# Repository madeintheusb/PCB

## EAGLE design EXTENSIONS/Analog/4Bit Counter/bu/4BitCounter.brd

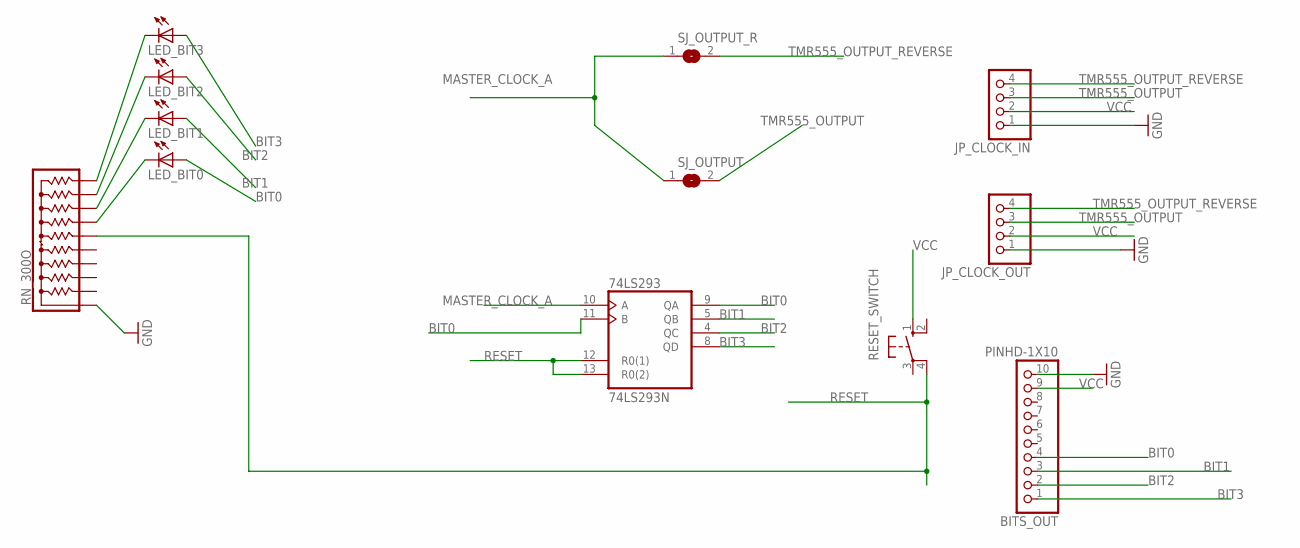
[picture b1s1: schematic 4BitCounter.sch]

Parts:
74LS293: 74LS293N; DIL14
BITS_OUT: PINHD-1X10; 1X10-BIG
JP_CLOCK_IN: PINHD-1X4; 1X04
JP_CLOCK_OUT: PINHD-1X4; 1X04
LED_BIT0, LED_BIT1, LED_BIT2, LED_BIT3: LEDSMT1206; 1206
RESET_SWITCH: 10-XX; B3F-10XX
RN_300O: 4610X; SIP10
SJ_OUTPUT: SOLDERJUMPERREFLOW; SOLDERJUMPER_REFLOW
SJ_OUTPUT_R: SOLDERJUMPERREFLOW; SOLDERJUMPER_REFLOW

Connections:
BIT0: 74LS293.9 (QA), 74LS293.11 (B), BITS_OUT.4, LED_BIT0.A
BIT1: 74LS293.5 (QB), BITS_OUT.3, LED_BIT1.A
BIT2: 74LS293.4 (QC), BITS_OUT.2, LED_BIT2.A
BIT3: 74LS293.8 (QD), BITS_OUT.1, LED_BIT3.A
GND: 74LS293.7 (GND), BITS_OUT.10, JP_CLOCK_IN.1, JP_CLOCK_OUT.1, RN_300O.1
MASTER_CLOCK_A: 74LS293.10 (A), SJ_OUTPUT.1, SJ_OUTPUT_R.1
unnamed: LED_BIT1.C, RN_300O.8
unnamed: LED_BIT0.C, RN_300O.7
unnamed: LED_BIT2.C, RN_300O.9
unnamed: LED_BIT3.C, RN_300O.10
RESET: 74LS293.12 (R0(1)), 74LS293.13 (R0(2)), RESET_SWITCH.4 (P1), RN_300O.6
TMR555_OUTPUT: JP_CLOCK_IN.3, JP_CLOCK_OUT.3, SJ_OUTPUT.2
TMR555_OUTPUT_REVERSE: JP_CLOCK_IN.4, JP_CLOCK_OUT.4, SJ_OUTPUT_R.2
VCC: 74LS293.14 (VCC), BITS_OUT.9, JP_CLOCK_IN.2, JP_CLOCK_OUT.2, RESET_SWITCH.1 (S)

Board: 2 copper layers, 12 parts (0 on the bottom side), 14 nets, no tracks yet.

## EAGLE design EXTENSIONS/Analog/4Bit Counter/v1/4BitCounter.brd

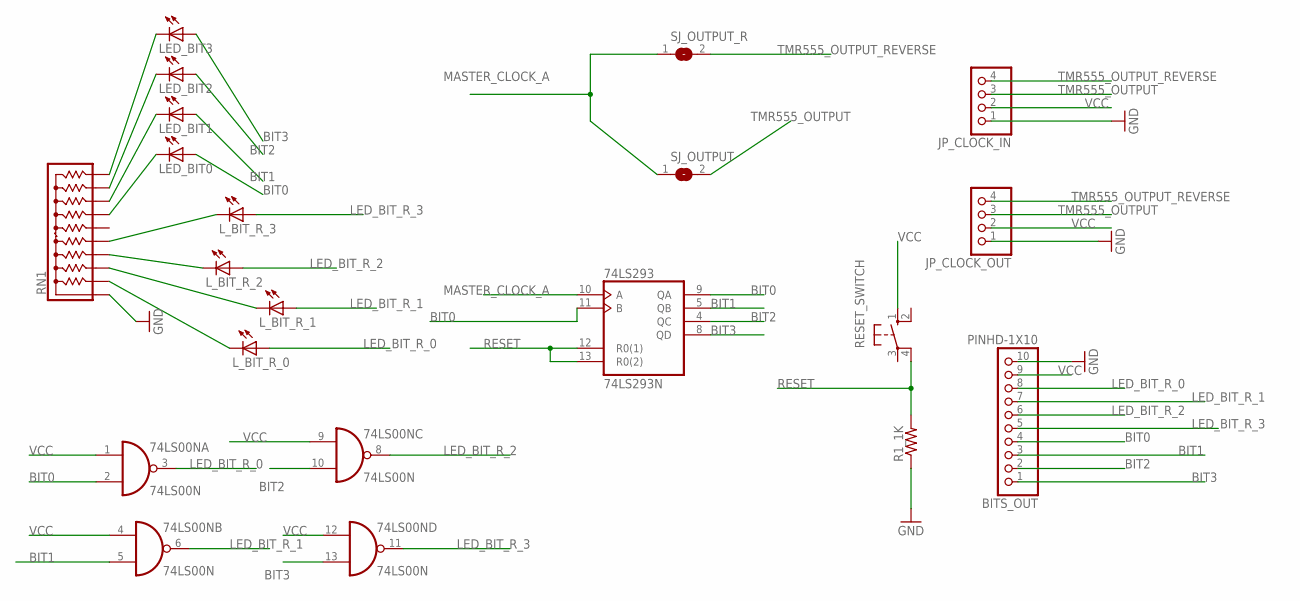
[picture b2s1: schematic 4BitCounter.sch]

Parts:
74LS00N: 74LS00N; DIL14
74LS293: 74LS293N; DIL14
BITS_OUT: PINHD-1X10; 1X10-BIG
JP_CLOCK_IN: PINHD-1X4; 1X04
JP_CLOCK_OUT: PINHD-1X4; 1X04
LED_BIT0, LED_BIT1, LED_BIT2, LED_BIT3: LEDSMT1206; 1206
L_BIT_R_0, L_BIT_R_1, L_BIT_R_2, L_BIT_R_3: LEDSMT1206; 1206
R1_1K: R-US_R1206; R1206
RESET_SWITCH: 10-XX; B3F-10XX
RN1: 4610X; SIP10
SJ_OUTPUT: SOLDERJUMPERREFLOW; SOLDERJUMPER_REFLOW
SJ_OUTPUT_R: SOLDERJUMPERREFLOW; SOLDERJUMPER_REFLOW

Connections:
BIT0: 74LS00N.2 (I1), 74LS293.9 (QA), 74LS293.11 (B), BITS_OUT.4, LED_BIT0.A
BIT1: 74LS00N.5 (I1), 74LS293.5 (QB), BITS_OUT.3, LED_BIT1.A
BIT2: 74LS00N.10 (I1), 74LS293.4 (QC), BITS_OUT.2, LED_BIT2.A
BIT3: 74LS00N.13 (I1), 74LS293.8 (QD), BITS_OUT.1, LED_BIT3.A
GND: 74LS00N.7 (GND), 74LS293.7 (GND), BITS_OUT.10, JP_CLOCK_IN.1, JP_CLOCK_OUT.1, R1_1K.1, RN1.1
LED_BIT_R_0: 74LS00N.3 (O), BITS_OUT.8, L_BIT_R_0.A
LED_BIT_R_1: 74LS00N.6 (O), BITS_OUT.7, L_BIT_R_1.A
LED_BIT_R_2: 74LS00N.8 (O), BITS_OUT.6, L_BIT_R_2.A
LED_BIT_R_3: 74LS00N.11 (O), BITS_OUT.5, L_BIT_R_3.A
MASTER_CLOCK_A: 74LS293.10 (A), SJ_OUTPUT.1, SJ_OUTPUT_R.1
unnamed: LED_BIT1.C, RN1.8
unnamed: LED_BIT0.C, RN1.7
unnamed: LED_BIT2.C, RN1.9
unnamed: LED_BIT3.C, RN1.10
unnamed: L_BIT_R_0.C, RN1.2
unnamed: L_BIT_R_1.C, RN1.3
unnamed: L_BIT_R_2.C, RN1.4
unnamed: L_BIT_R_3.C, RN1.5
RESET: 74LS293.12 (R0(1)), 74LS293.13 (R0(2)), R1_1K.2, RESET_SWITCH.4 (P1)
TMR555_OUTPUT: JP_CLOCK_IN.3, JP_CLOCK_OUT.3, SJ_OUTPUT.2
TMR555_OUTPUT_REVERSE: JP_CLOCK_IN.4, JP_CLOCK_OUT.4, SJ_OUTPUT_R.2
VCC: 74LS00N.1 (I0), 74LS00N.4 (I0), 74LS00N.9 (I0), 74LS00N.12 (I0), 74LS00N.14 (VCC), 74LS293.14 (VCC), BITS_OUT.9, JP_CLOCK_IN.2, JP_CLOCK_OUT.2, RESET_SWITCH.1 (S)

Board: 2 copper layers, 18 parts (0 on the bottom side), 22 nets, no tracks yet.

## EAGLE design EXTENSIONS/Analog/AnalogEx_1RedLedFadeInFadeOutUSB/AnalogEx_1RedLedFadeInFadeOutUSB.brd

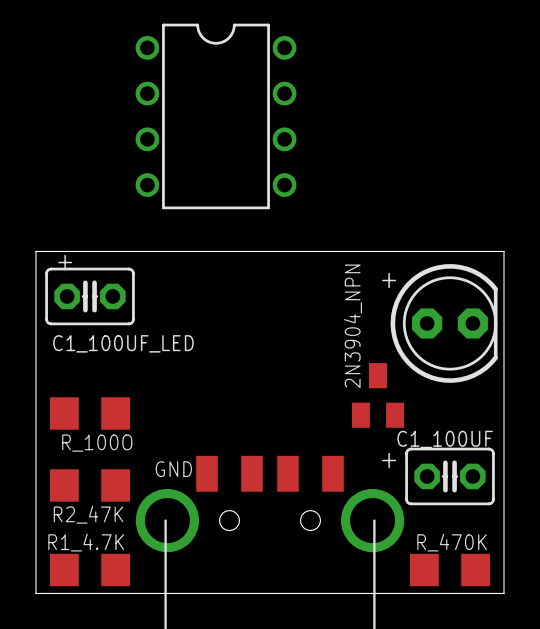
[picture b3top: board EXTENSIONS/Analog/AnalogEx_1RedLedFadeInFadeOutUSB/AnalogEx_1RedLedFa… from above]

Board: 2 copper layers, 26.0 x 19.0 mm, 10 parts (0 on the bottom side), 8 nets, no tracks yet.

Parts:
2N3904_NPN: SOT23-BEC
C1_100UF, C1_100UF_LED: C025-030X050
IC1: NE555N; DIL08
R1_4.7K, R2_47K: R1206
RED_LED: LED5MM
R_100O, R_470K: R1206
X1: USB-A; MOLEX_480371000

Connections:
GND: 2N3904_NPN.E, C1_100UF.1, IC1.1, R_100O.1, X1.4
unnamed: IC1.7, R1_4.7K.1, R2_47K.2
unnamed: C1_100UF_LED.2, R_100O.2
unnamed: 2N3904_NPN.B, C1_100UF_LED.1, R_470K.2
unnamed: 2N3904_NPN.C, RED_LED.K
THRESHOLD: C1_100UF.2, IC1.2, IC1.6, R2_47K.1
TMR555_OUTPUT: IC1.3, R_470K.1
VCC: IC1.4, IC1.8, R1_4.7K.2, RED_LED.A, X1.1

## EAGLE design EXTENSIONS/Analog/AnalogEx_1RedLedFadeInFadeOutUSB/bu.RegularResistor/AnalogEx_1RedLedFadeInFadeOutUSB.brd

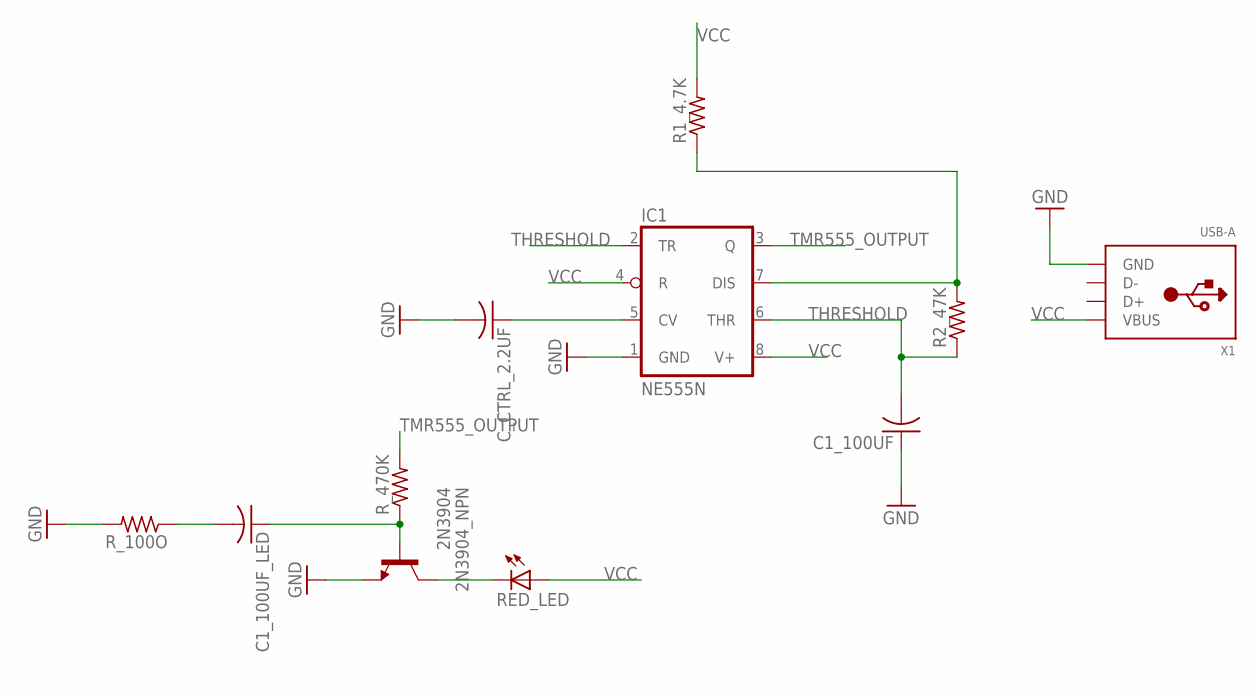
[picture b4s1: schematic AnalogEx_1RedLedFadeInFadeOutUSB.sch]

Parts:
2N3904_NPN: 2N3904; TO92
C1_100UF, C1_100UF_LED: C-US025-030X050; C025-030X050
C_CTRL_2.2UF: C-US025-030X050; C025-030X050
IC1: NE555N; DIL08
R1_4.7K, R2_47K: R-US_0207/10; 0207/10
RED_LED: LED5MM
R_100O, R_470K: R-US_0207/10; 0207/10
X1: USB-A; MOLEX_480371000

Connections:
GND: 2N3904_NPN.3 (E), C1_100UF.1, C_CTRL_2.2UF.2, IC1.1 (GND), R_100O.2, X1.4 (GND)
unnamed: IC1.7 (DIS), R1_4.7K.1, R2_47K.2
unnamed: C_CTRL_2.2UF.1, IC1.5 (CV)
unnamed: 2N3904_NPN.2 (B), C1_100UF_LED.1, R_470K.1
unnamed: 2N3904_NPN.1 (C), RED_LED.K (C)
unnamed: C1_100UF_LED.2, R_100O.1
THRESHOLD: C1_100UF.2, IC1.2 (TR), IC1.6 (THR), R2_47K.1
TMR555_OUTPUT: IC1.3 (Q), R_470K.2
VCC: IC1.4 (R), IC1.8 (V+), R1_4.7K.2, RED_LED.A, X1.1 (VBUS)

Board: 2 copper layers, 11 parts (0 on the bottom side), 9 nets, no tracks yet.

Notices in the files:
parts and their libraries:
microbuilder: This work is placed in the public domain, and may be freely used for commercial and non-commercial work with the following conditions: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
